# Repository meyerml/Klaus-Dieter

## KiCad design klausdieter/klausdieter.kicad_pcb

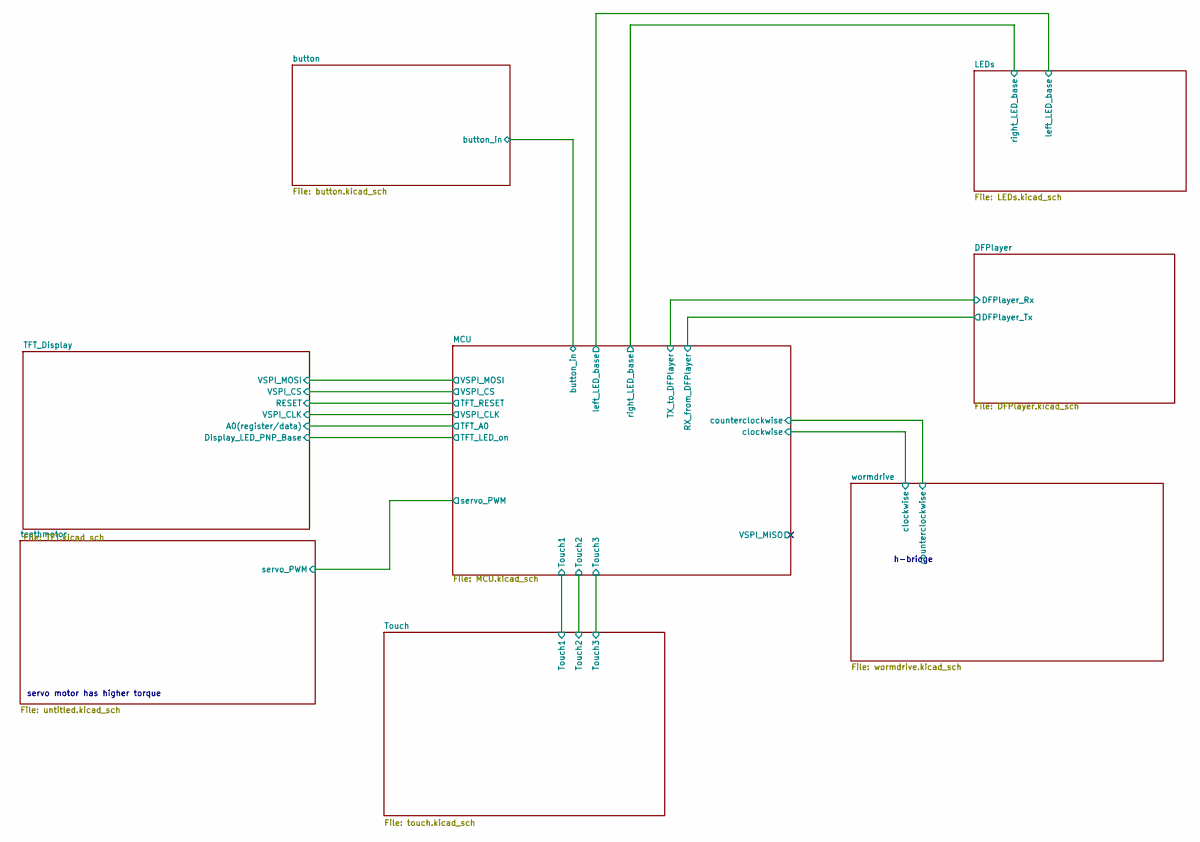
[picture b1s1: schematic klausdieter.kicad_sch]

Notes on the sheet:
servo motor has higher torque
h-bridge

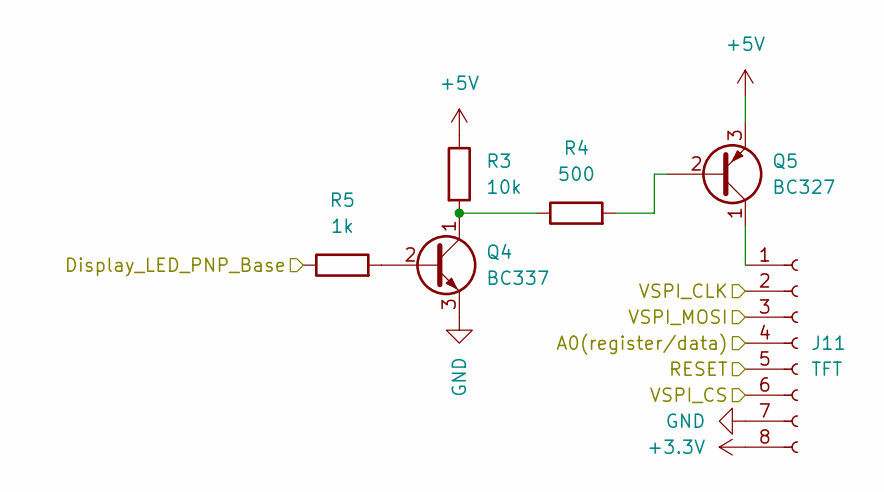
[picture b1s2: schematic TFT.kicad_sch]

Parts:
J11: TFT; PinSocket_1x08_P2.54mm_Vertical
Q4: BC337; TO-92
Q5: BC327; TO-92
R3: 10k; R_Axial_DIN0204_L3.6mm_D1.6mm_P5.08mm_Horizontal
R4: 500; R_Axial_DIN0204_L3.6mm_D1.6mm_P5.08mm_Horizontal
R5: 1k; R_Axial_DIN0204_L3.6mm_D1.6mm_P5.08mm_Horizontal

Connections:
+3.3V: J11.8; also elsewhere on the board
+5V: Q5.3 (E), R3.1; also elsewhere on the board
/MCU/TFT_A0: J11.4; also elsewhere on the board
/MCU/TFT_LED_on: R5.1; also elsewhere on the board
/MCU/TFT_RESET: J11.5; also elsewhere on the board
/MCU/VSPI_CLK: J11.2; also elsewhere on the board
/MCU/VSPI_CS: J11.6; also elsewhere on the board
/MCU/VSPI_MOSI: J11.3; also elsewhere on the board
GND: J11.7, Q4.3 (E); also elsewhere on the board
unnamed: J11.1, Q5.1 (C)
unnamed: Q4.2 (B), R5.2
unnamed: Q4.1 (C), R3.2, R4.1
unnamed: Q5.2 (B), R4.2

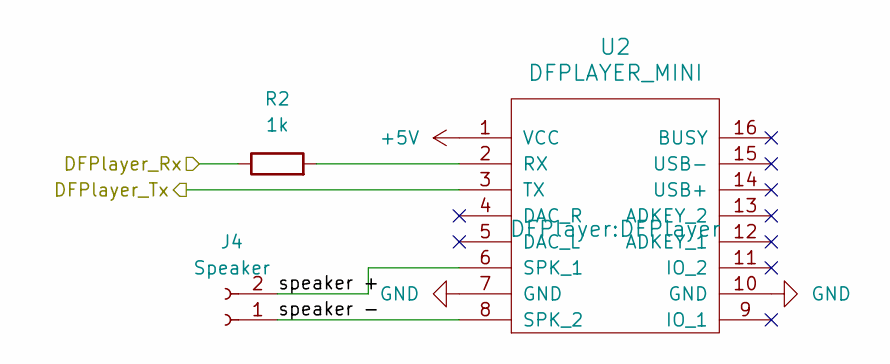
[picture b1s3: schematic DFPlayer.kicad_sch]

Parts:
J4: Speaker; PinSocket_1x02_P2.54mm_Vertical
R2: 1k; R_Axial_DIN0204_L3.6mm_D1.6mm_P5.08mm_Horizontal
U2: DFPLAYER_MINI; DFPlayer

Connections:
+5V: U2.1 (VCC); also elsewhere on the board
/DFPlayer/DFPlayer_Rx: R2.1; also elsewhere on the board
/DFPlayer/DFPlayer_Tx: U2.3 (TX); also elsewhere on the board
/DFPlayer/speaker +: J4.2, U2.6 (SPK_1)
/DFPlayer/speaker -: J4.1, U2.8 (SPK_2)
GND: U2.7 (GND), U2.10 (GND); also elsewhere on the board
unnamed: R2.2, U2.2 (RX)

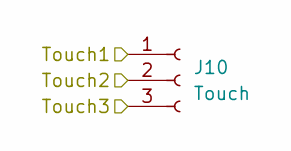
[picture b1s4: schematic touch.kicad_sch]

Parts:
J10: Touch; PinSocket_1x03_P2.54mm_Vertical

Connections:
/MCU/Touch1: J10.1; also elsewhere on the board
/MCU/Touch2: J10.2; also elsewhere on the board
/MCU/Touch3: J10.3; also elsewhere on the board

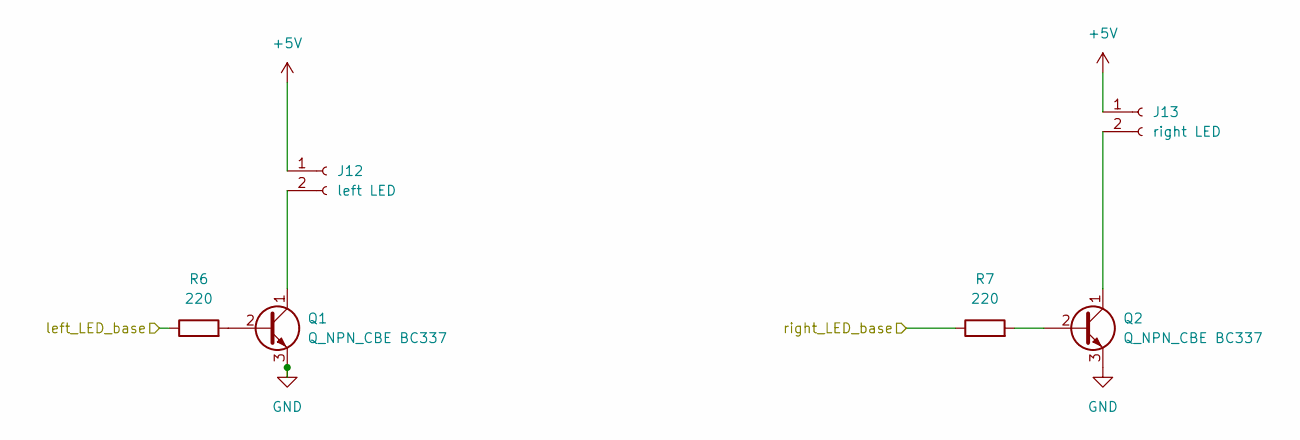
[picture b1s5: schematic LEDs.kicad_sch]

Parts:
J12: left LED; PinSocket_1x02_P2.54mm_Vertical
J13: right LED; PinSocket_1x02_P2.54mm_Vertical
Q1, Q2: Q_NPN_CBE BC337; TO-92
R6, R7: 220; R_Axial_DIN0204_L3.6mm_D1.6mm_P5.08mm_Horizontal

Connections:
+5V: J12.1, J13.1; also elsewhere on the board
/LEDs/left_LED_base: R6.1; also elsewhere on the board
/LEDs/right_LED_base: R7.1; also elsewhere on the board
GND: Q1.3 (E), Q2.3 (E); also elsewhere on the board
unnamed: J12.2, Q1.1 (C)
unnamed: J13.2, Q2.1 (C)
unnamed: Q1.2 (B), R6.2
unnamed: Q2.2 (B), R7.2

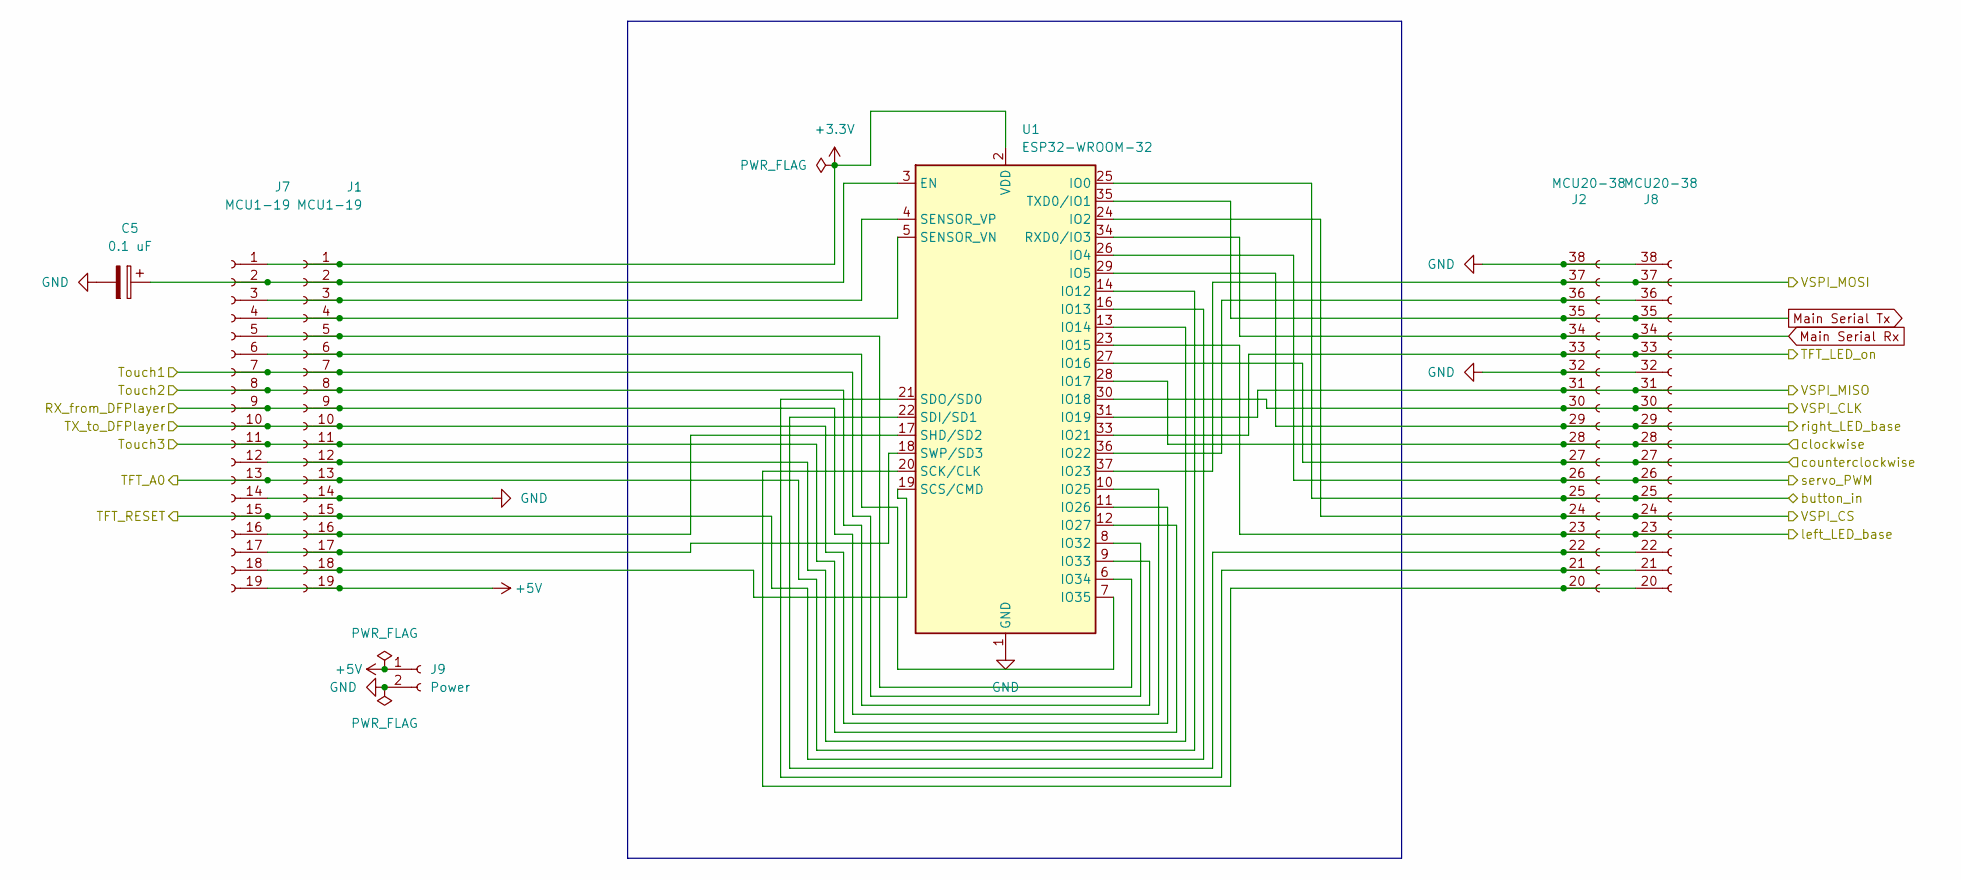
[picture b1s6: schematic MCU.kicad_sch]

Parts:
C5: 0.1 uF; CP_Radial_D5.0mm_P2.50mm
J1, J7: MCU1-19; PinHeader_1x19_P2.54mm_Vertical
J2, J8: MCU20-38; PinSocket_1x19_P2.54mm_Vertical_renumbered
J9: Power; PinSocket_1x02_P2.54mm_Vertical
U1: ESP32-WROOM-32; MODULE_ESP32_NODEMCU-USB-C

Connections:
+3.3V: J1.1, J7.1, U1.2 (VDD); also elsewhere on the board
+5V: J1.19, J7.19, J9.1; also elsewhere on the board
/DFPlayer/DFPlayer_Rx: J1.10, J7.10, U1.11 (IO26); also elsewhere on the board
/DFPlayer/DFPlayer_Tx: J1.9, J7.9, U1.10 (IO25); also elsewhere on the board
/LEDs/left_LED_base: J2.23, J8.23, U1.23 (IO15); also elsewhere on the board
/LEDs/right_LED_base: J2.29, J8.29, U1.29 (IO5); also elsewhere on the board
/MCU/TFT_A0: J1.13, J7.13, U1.14 (IO12); also elsewhere on the board
/MCU/TFT_LED_on: J2.33, J8.33, U1.33 (IO21); also elsewhere on the board
/MCU/TFT_RESET: J1.15, J7.15, U1.16 (IO13); also elsewhere on the board
/MCU/Touch1: J1.7, J7.7, U1.8 (IO32); also elsewhere on the board
/MCU/Touch2: J1.8, J7.8, U1.9 (IO33); also elsewhere on the board
/MCU/Touch3: J1.11, J7.11, U1.12 (IO27); also elsewhere on the board
/MCU/VSPI_CLK: J2.30, J8.30, U1.30 (IO18); also elsewhere on the board
/MCU/VSPI_CS: J2.24, J8.24, U1.24 (IO2); also elsewhere on the board
/MCU/VSPI_MISO: J2.31, J8.31, U1.31 (IO19)
/MCU/VSPI_MOSI: J2.37, J8.37, U1.37 (IO23); also elsewhere on the board
/MCU/button_in: J2.25, J8.25, U1.25 (IO0); also elsewhere on the board
/MCU/clockwise: J2.28, J8.28, U1.28 (IO17); also elsewhere on the board
/MCU/counterclockwise: J2.27, J8.27, U1.27 (IO16); also elsewhere on the board
/MCU/servo_PWM: J2.26, J8.26, U1.26 (IO4); also elsewhere on the board
GND: C5.2, J1.14, J2.32, J2.38, J7.14, J8.32, J8.38, J9.2, U1.1 (GND), U1.15 (GND), U1.38 (GND), U1.39 (GND); also elsewhere on the board
Main Serial Rx: J2.34, J8.34, U1.34 (RXD0/IO3)
Main Serial Tx: J2.35, J8.35, U1.35 (TXD0/IO1)
unnamed: C5.1, J1.2, J7.2, U1.3 (EN)
unnamed: J1.3, J7.3, U1.4 (SENSOR_VP)
unnamed: J1.4, J7.4, U1.5 (SENSOR_VN)
unnamed: J1.5, J7.5, U1.6 (IO34)
unnamed: J1.6, J7.6, U1.7 (IO35)
unnamed: J1.12, J7.12, U1.13 (IO14)
unnamed: J1.16, J7.16, U1.17 (SHD/SD2)
unnamed: J1.17, J7.17, U1.18 (SWP/SD3)
unnamed: J1.18, J7.18, U1.19 (SCS/CMD)
unnamed: J2.20, J8.20, U1.20 (SCK/CLK)
unnamed: J2.21, J8.21, U1.21 (SDO/SD0)
unnamed: J2.22, J8.22, U1.22 (SDI/SD1)
unnamed: J2.36, J8.36, U1.36 (IO22)

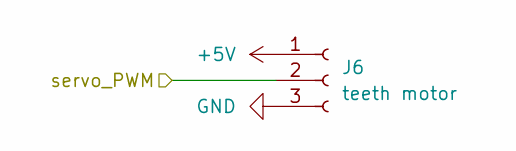
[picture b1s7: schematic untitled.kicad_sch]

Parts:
J6: teeth motor; PinSocket_1x03_P2.54mm_Vertical

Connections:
+5V: J6.1; also elsewhere on the board
/MCU/servo_PWM: J6.2; also elsewhere on the board
GND: J6.3; also elsewhere on the board

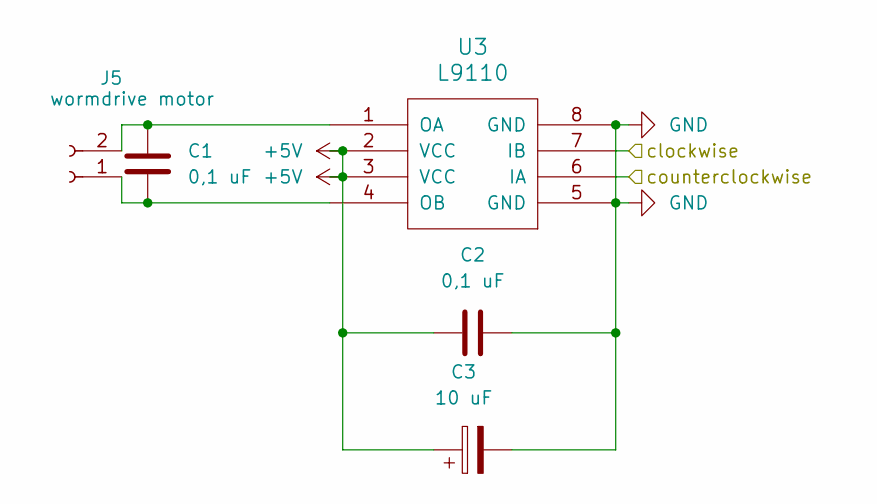
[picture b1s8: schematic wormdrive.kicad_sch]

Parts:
C1, C2: 0,1 uF; C_Disc_D5.0mm_W2.5mm_P2.50mm
C3: 10 uF; CP_Radial_D5.0mm_P2.50mm
J5: wormdrive motor; PinSocket_1x02_P2.54mm_Vertical
U3: L9110; CERDIP-8_W7.62mm_SideBrazed

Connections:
+5V: C2.2, C3.1, U3.2 (VCC), U3.3 (VCC); also elsewhere on the board
/MCU/clockwise: U3.7 (IB); also elsewhere on the board
/MCU/counterclockwise: U3.6 (IA); also elsewhere on the board
GND: C2.1, C3.2, U3.5 (GND), U3.8 (GND); also elsewhere on the board
unnamed: C1.2, J5.1, U3.4 (OB)
unnamed: C1.1, J5.2, U3.1 (OA)

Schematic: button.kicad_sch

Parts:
J3: Button; PinSocket_1x02_P2.54mm_Vertical
R1: 10k; R_Axial_DIN0204_L3.6mm_D1.6mm_P5.08mm_Horizontal
SW1: SW_Push

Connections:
+3.3V: R1.1; also elsewhere on the board
/MCU/button_in: J3.1, R1.2, SW1.1; also elsewhere on the board
GND: J3.2, SW1.2; also elsewhere on the board

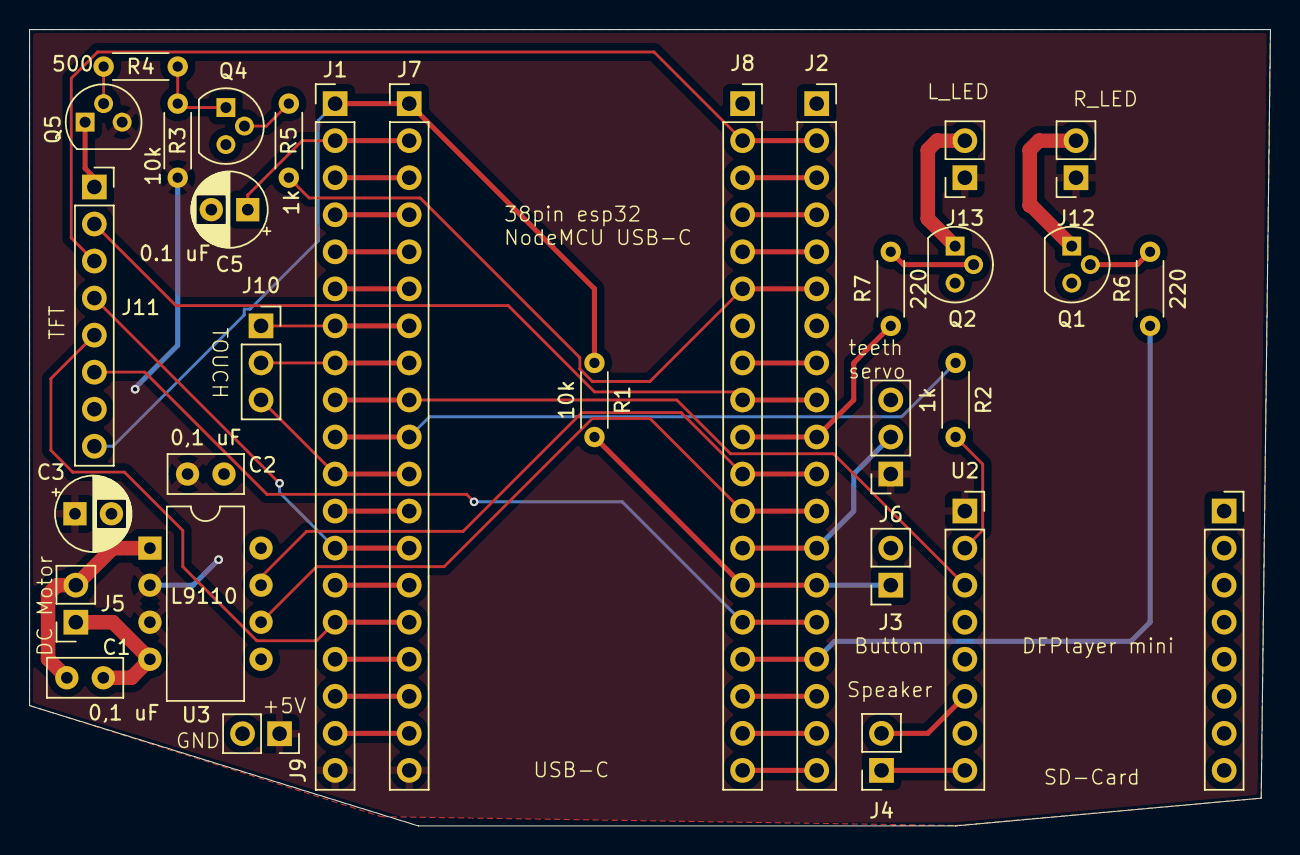
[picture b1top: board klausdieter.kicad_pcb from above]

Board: 2 copper layers, 85.1 x 54.6 mm, 30 parts (0 on the bottom side), 49 nets.

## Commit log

2025-11-16 add all files to github
